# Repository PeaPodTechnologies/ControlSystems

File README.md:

# PeaPod Microcontroller Software

A library written in Arduino C++ for modular plug-and-play low-level control systems through a high-level API. Implemented with PlatformIO and tested on AVR.

# Overview

The goals of this library are threefold:
1. Error-free asynchronous communication with a **dynamic** list of multiplexers and I2C devices;
2. **Abstraction** from those multiplexer groups into hot-swappable `Module`s, and I2C devices into `Sensor`s (environment variable *getters*) and `Actuator`s (environment variable *setters*);
3. **Mapping** together `Sensor`s and `Actuator`s into coherent `ControlSystem`s: feedback systems, each with a "parameter" that can be set as the target value of the environment variable of interest;

## Installation
> This will eventually be migrated to an Arduino library. For now, see #Development##Installation

# Development

## Testing

`pio test -e peapod`

## API

### Object Instance Tree
```
PeaPod (God Object)
|-ControlSystem*'s HashMap (for instruction handling & calculation)
| |-Control Systems [key: environment variable being controlled]
|   |-Sensor* (envvar getter)
|   |-Actuator* (envvar setter)
|   |-parameter (string)
|   |-target    (float)
|
|-Module List (hardware state change tracking -> Interface lifecycle management)
| |-Sensor* Array
| |-Actuator* Array
| |-Interface* Array (support)
| |-array lengths (byte)
```

### Inheritance Tree

```
Interface
|-ADC
|-EEPROM
|-GPIO
|-PWM
|-Any I2C Sensors/Actuators (multiple inheritance)

Module (MUX device)

Sensor
|-All Sensors

Actuator
|-All Actuators
```

### Dependency Summary

> Not including external libraries or `utils/`.

```
Interface
|-MUX (also included in Interface)
|-All other interfaces
|-All I2C Sensors/Actuators
```

## Style Guide

- Sensor and actuator instance-related code should not be const
- Static API code (i.e. ids, factories) should be const (and preferrably PROGMEM)
- Avoid passing around pointers to const pointers. It's already const.

## Hardware Spec

### Connector Pinouts

- I2C: JST SH 1.00mm 4-pin (1: GND, 2: +5V, 3: SDA, 4: SCL)
- Middleware Output Signals: Molex Micro-Lock PLUS 2-pin (1: Signal, 2: GND)
- Endware Recieving Signals: Molex Micro-Lock PLUS 2-pin (1: GND, 2: Signal)
- Power: Molex Micro-Fit 3.0 2-pin (1: GND, 2: VCC)

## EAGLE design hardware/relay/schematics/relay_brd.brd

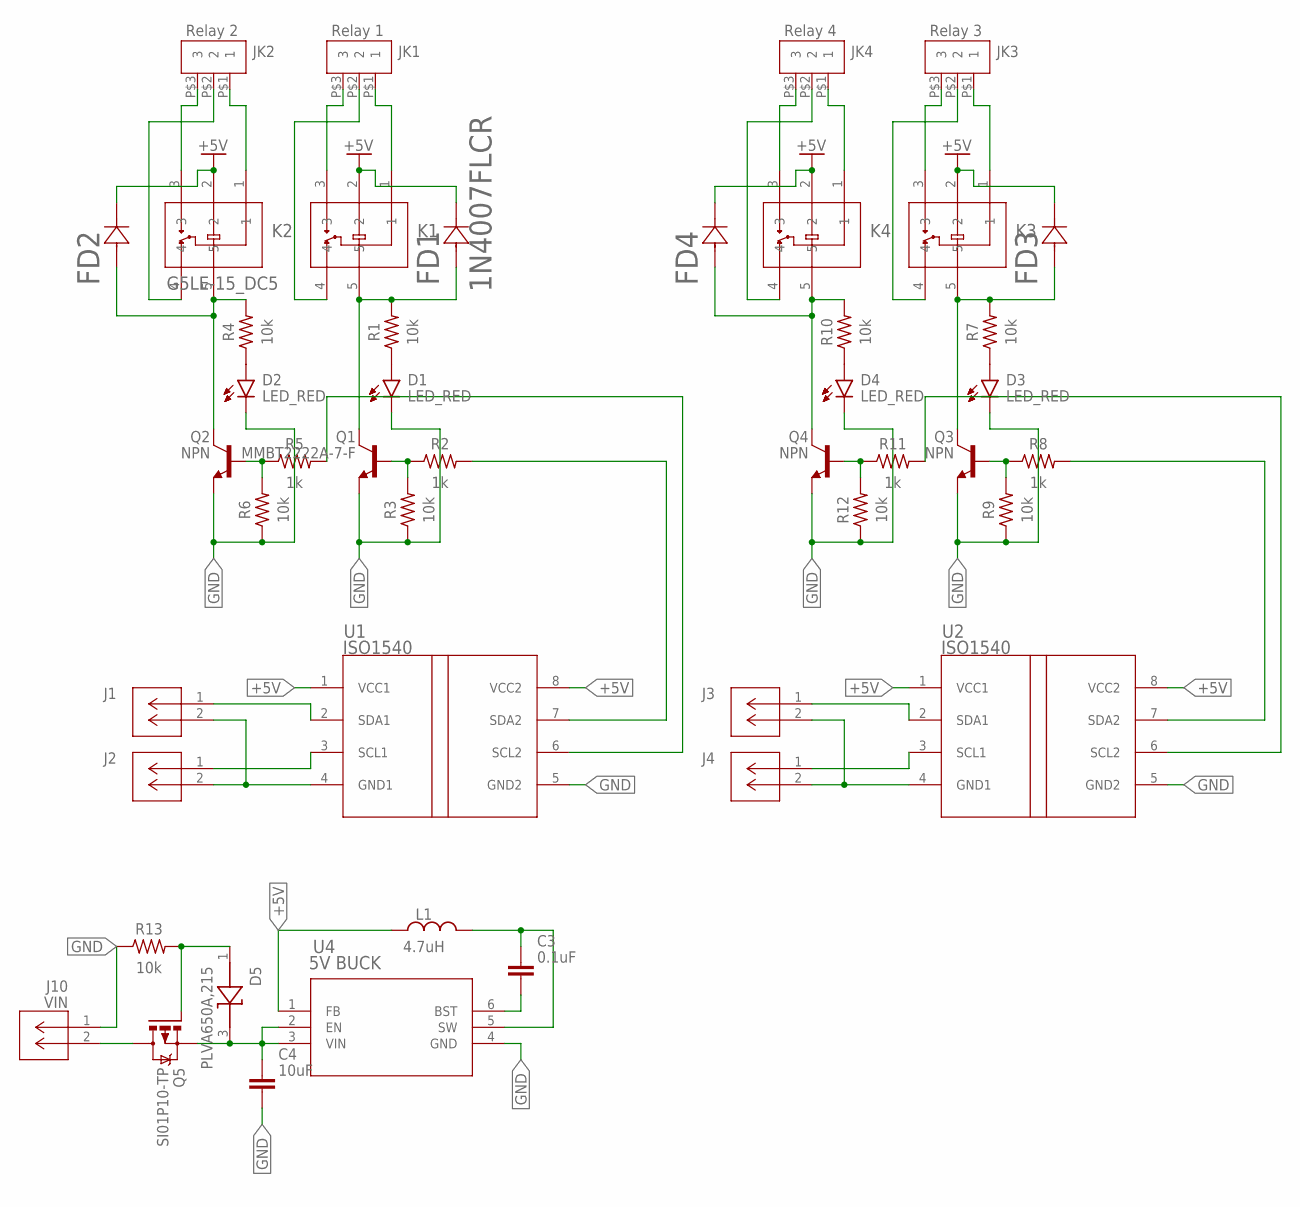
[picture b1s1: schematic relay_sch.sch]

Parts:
C3: 0.1uF; CAPC1608X85
C4: 10uF; CAPC1608X85
D1, D2, D3, D4: LED_RED; LEDC1608X55N_FLAT-R
D5: PLVA650A,215; SOT95P230X110-3N
FD1: 1N4007FLCR; CR_SOD-123FL_SME-L
FD2, FD3, FD4: 1N4007FLCR_SOD-123FL_SME-L; CR_SOD-123FL_SME-L
J1, J2, J3, J4: MICROLOCK-2PIN; 2PIN
J10: VIN; 2PIN
JK1: Relay 1; TERM-3,5MM
JK2: Relay 2; TERM-3,5MM
JK3: Relay 3; TERM-3,5MM
JK4: Relay 4; TERM-3,5MM
K1, K3, K4: G5LE-14_DC12RELAY_G5LE-1_DC5_OMR; RELAY_G5LE-1_DC5_OMR
K2: G5LE-15_DC5; RELAY_G5LE-1_DC5_OMR
L1: 4.7uH; INDC1608X95N
Q1: MMBT2222A-7-F; SOT95P237X112-3N
Q2, Q3, Q4: NPN; SOT95P237X112-3N
Q5: SI01P10-TP; SOT23
R1, R4, R7, R10: 10k; RESC2012X65
R2, R5, R8, R11: 1k; RESC1608X60
R3, R6, R9, R12, R13: 10k; RESC1608X60
U1, U2: ISO1540; SOIC-8
U4: 5V BUCK; AP63205

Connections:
+5V: FD1.1 (CATHODE), FD2.1 (CATHODE), FD3.1 (CATHODE), FD4.1 (CATHODE), K1.2, K2.2, K3.2, K4.2, L1.1, U1.1 (VCC1), U1.8 (VCC2), U2.1 (VCC1), U2.8 (VCC2), U4.1 (FB)
GND: C4.2, D1.C, D2.C, D3.C, D4.C, J10.1, Q1.2 (E), Q2.2 (E), Q3.2 (E), Q4.2 (E), R3.1, R6.1, R9.1, R12.1, R13.1, U1.5 (GND2), U2.5 (GND2), U4.4 (GND)
unnamed: JK1.P$3 (3), K1.3
unnamed: JK1.P$1 (1), K1.1
unnamed: JK1.P$2 (2), K1.4
unnamed: FD1.2 (ANODE), K1.5, Q1.3 (C), R1.2
unnamed: FD2.2 (ANODE), K2.5, Q2.3 (C), R4.2
unnamed: Q1.1 (B), R2.1, R3.2
unnamed: JK2.P$3 (3), K2.3
unnamed: R2.2, U1.7 (SDA2)
unnamed: J1.1 (2), U1.2 (SDA1)
unnamed: J2.1 (2), U1.3 (SCL1)
unnamed: J1.2 (3), J2.2 (3), U1.4 (GND1)
unnamed: JK2.P$1 (1), K2.1
unnamed: FD4.2 (ANODE), K4.5, Q4.3 (C), R10.2
unnamed: FD3.2 (ANODE), K3.5, Q3.3 (C), R7.2
unnamed: Q2.1 (B), R5.1, R6.2
unnamed: JK2.P$2 (2), K2.4
unnamed: R5.2, U1.6 (SCL2)
unnamed: JK3.P$3 (3), K3.3
unnamed: JK3.P$1 (1), K3.1
unnamed: D2.A, R4.1
unnamed: D3.A, R7.1
unnamed: Q3.1 (B), R8.1, R9.2
unnamed: JK3.P$2 (2), K3.4
unnamed: J3.1 (2), U2.2 (SDA1)
unnamed: R8.2, U2.7 (SDA2)
unnamed: J4.1 (2), U2.3 (SCL1)
unnamed: J3.2 (3), J4.2 (3), U2.4 (GND1)
unnamed: JK4.P$3 (3), K4.3
unnamed: JK4.P$1 (1), K4.1
unnamed: D1.A, R1.1
unnamed: D4.A, R10.1
unnamed: Q4.1 (B), R11.1, R12.2
unnamed: JK4.P$2 (2), K4.4
unnamed: R11.2, U2.6 (SCL2)
unnamed: C3.2, U4.6 (BST)
unnamed: C3.1, L1.2, U4.5 (SW)
unnamed: J10.2, Q5.3 (D)
unnamed: C4.1, D5.3 (C), Q5.2 (S), U4.2 (EN), U4.3 (VIN)
unnamed: D5.1 (A), Q5.1 (G), R13.2

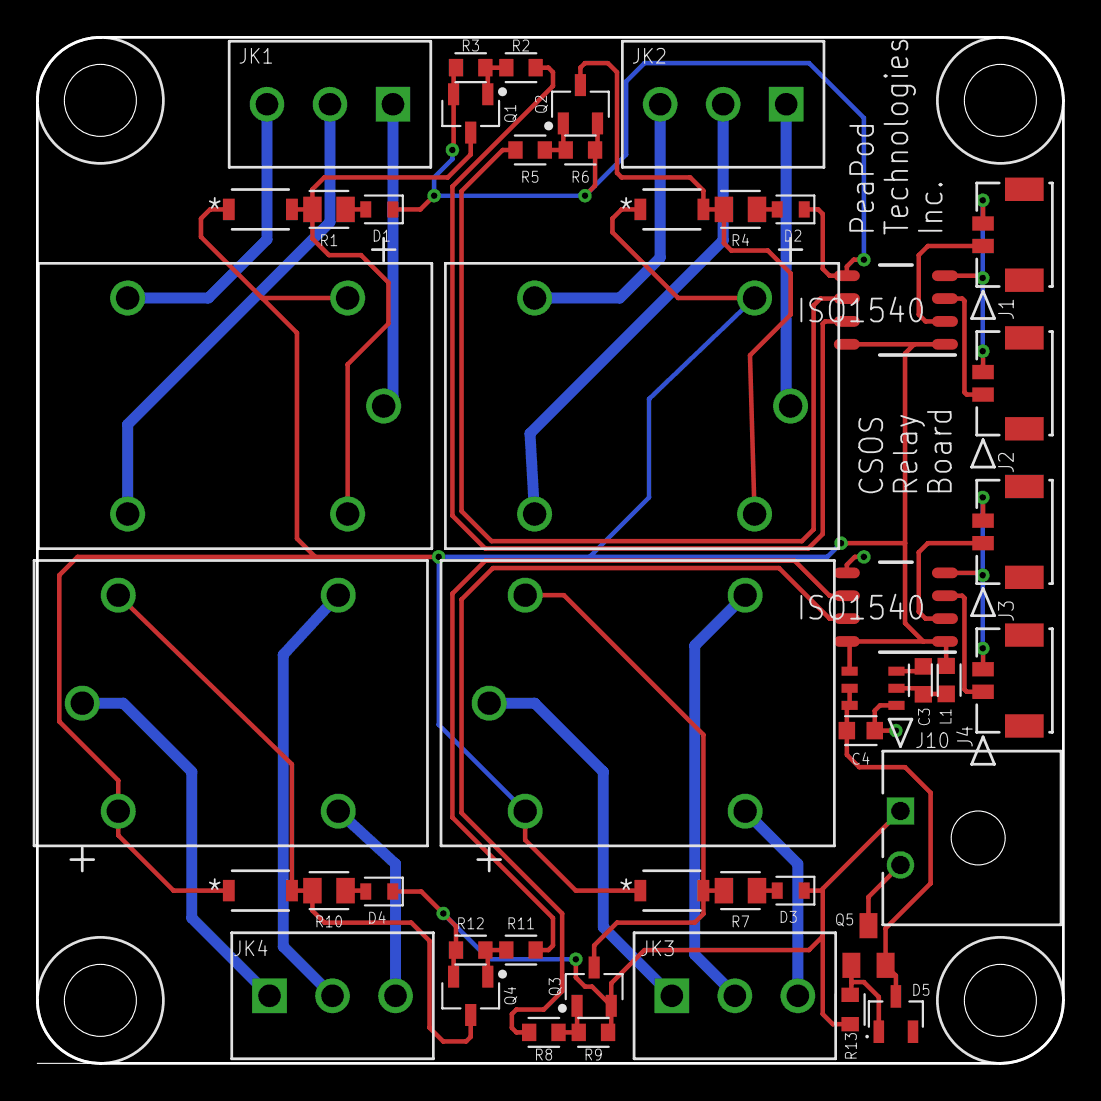
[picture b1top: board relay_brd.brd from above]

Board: 2 copper layers, 57.0 x 57.0 mm, 46 parts (0 on the bottom side), 41 nets.

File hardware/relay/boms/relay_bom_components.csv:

Index,Manufacturer Part Number,Manufacturer Name,Requested Quantity 1,Pack Quantity 1,Pack Type 1,Digi-Key Part Number 1,Unit Price 1,Extended Price 1,Minimum Order Quantity 1,Reference Designator,Product Notes
1,"PLVA650A,215",Nexperia USA Inc.,1,1,Cut Tape (CT),1727-5167-1-ND,0.65000,$0.65,1,D5,
2,SI01P10-TP,Micro Commercial Co,1,1,Cut Tape (CT),353-SI01P10-TPCT-ND,0.59000,$0.59,1,Q5,
3,AP63205WU-7,Diodes Incorporated,1,1,Cut Tape (CT),AP63205WU-7DICT-ND,1.33000,$1.33,1,U4,
4,0436500201,Molex,1,1,Tray,WM1865-ND,2.00000,$2.00,1,J10,
5,G5LE-14 DC5,Omron Electronics Inc-EMC Div,4,4,Tray,Z1011-ND,2.38000,$9.52,1,"K1,K2,K3,K4",
6,1N4007FL,SMC Diode Solutions,4,4,Cut Tape (CT),1655-1N4007FLCT-ND,0.19000,$0.76,1,"FD1,FD2,FD3,FD4",
7,ISO1540D,Texas Instruments,2,2,Tube,296-34896-5-ND,9.46000,$18.92,1,"U1,U2",
8,5055670271,Molex,4,4,Cut Tape (CT),WM17038CT-ND,1.32000,$5.28,1,"J1,J2,J3,J4",
9,0393570003,Molex,4,4,Bag,WM7878-ND,2.67000,$10.68,1,"JK1,JK2,JK3,JK4",
10,CL10B104KB8NNWC,Samsung Electro-Mechanics,1,1,Cut Tape (CT),1276-1935-1-ND,0.14000,$0.14,1,C3,
11,LQM18PH4R7MFRL,Murata Electronics,1,1,Cut Tape (CT),490-LQM18PH4R7MFRLCT-ND,0.57000,$0.57,1,L1,
12,CL10A106MQ8NNNC,Samsung Electro-Mechanics,1,1,Cut Tape (CT),1276-1119-1-ND,0.16000,$0.16,1,C4,
13,MMBT2222A-7-F,Diodes Incorporated,4,4,Cut Tape (CT),MMBT2222A-FDICT-ND,0.21000,$0.84,1,"Q1,Q2,Q3,Q4",
14,LTST-C191KRKT,Lite-On Inc.,4,4,Cut Tape (CT),160-1447-1-ND,0.40000,$1.60,1,"D1,D2,D3,D4",
15,RC0603FR-0710KL,YAGEO,5,5,Cut Tape (CT),311-10.0KHRCT-ND,0.15000,$0.75,1,"R3,R6,R9,R12,R13",
16,RC0805FR-0710KL,YAGEO,4,4,Cut Tape (CT),311-10.0KCRCT-ND,0.15000,$0.60,1,"R1,R4,R7,R10",
17,RC0603FR-071KL,YAGEO,4,4,Cut Tape (CT),311-1.00KHRCT-ND,0.15000,$0.60,1,"R2,R5,R8,R11",

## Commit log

2022-11-04 Static Library Structure
2022-11-10 CSOS v0.1.1 - GPIO, PWM, ADC Libraries
2023-09-10 Integration WIP
2023-10-20 Integration WIP 3
2023-10-25 INTEGRATED I2CIP
2023-10-26 SHT31 and FSM Chronograph
2023-10-26 Basic Example, Bugfix
2024-01-11 WIP #1
2024-02-22 Simple PeaPod :)
2024-04-06 Relay Board and Docs V1

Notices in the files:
parts and their libraries:
COPYRIGHT: Copyright (C) 2022 Ultra Librarian. All rights reserved.
COPYRIGHT: Copyright (C) 2024 Ultra Librarian. All rights reserved.
